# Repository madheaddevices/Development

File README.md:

# Development
 - Under development files
 - Default configuration files
 - In-progress designs

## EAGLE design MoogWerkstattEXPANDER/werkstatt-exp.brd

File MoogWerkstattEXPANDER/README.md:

These files are usable for making an Expander for Moog Werkstatt synthesizer.
First of all, the schematic made in Eagle, included the PCB placing, without tracing.
Second, the manufacturing files are loadable to JLCPCB online PCB ordering service.

BOM:
1. Thonkiconn Jack sockets: https://www.thonk.co.uk/shop/3-5mm-jacks/
2. 1x20 pinheader

Tamás Fejes, 14.12.2021.

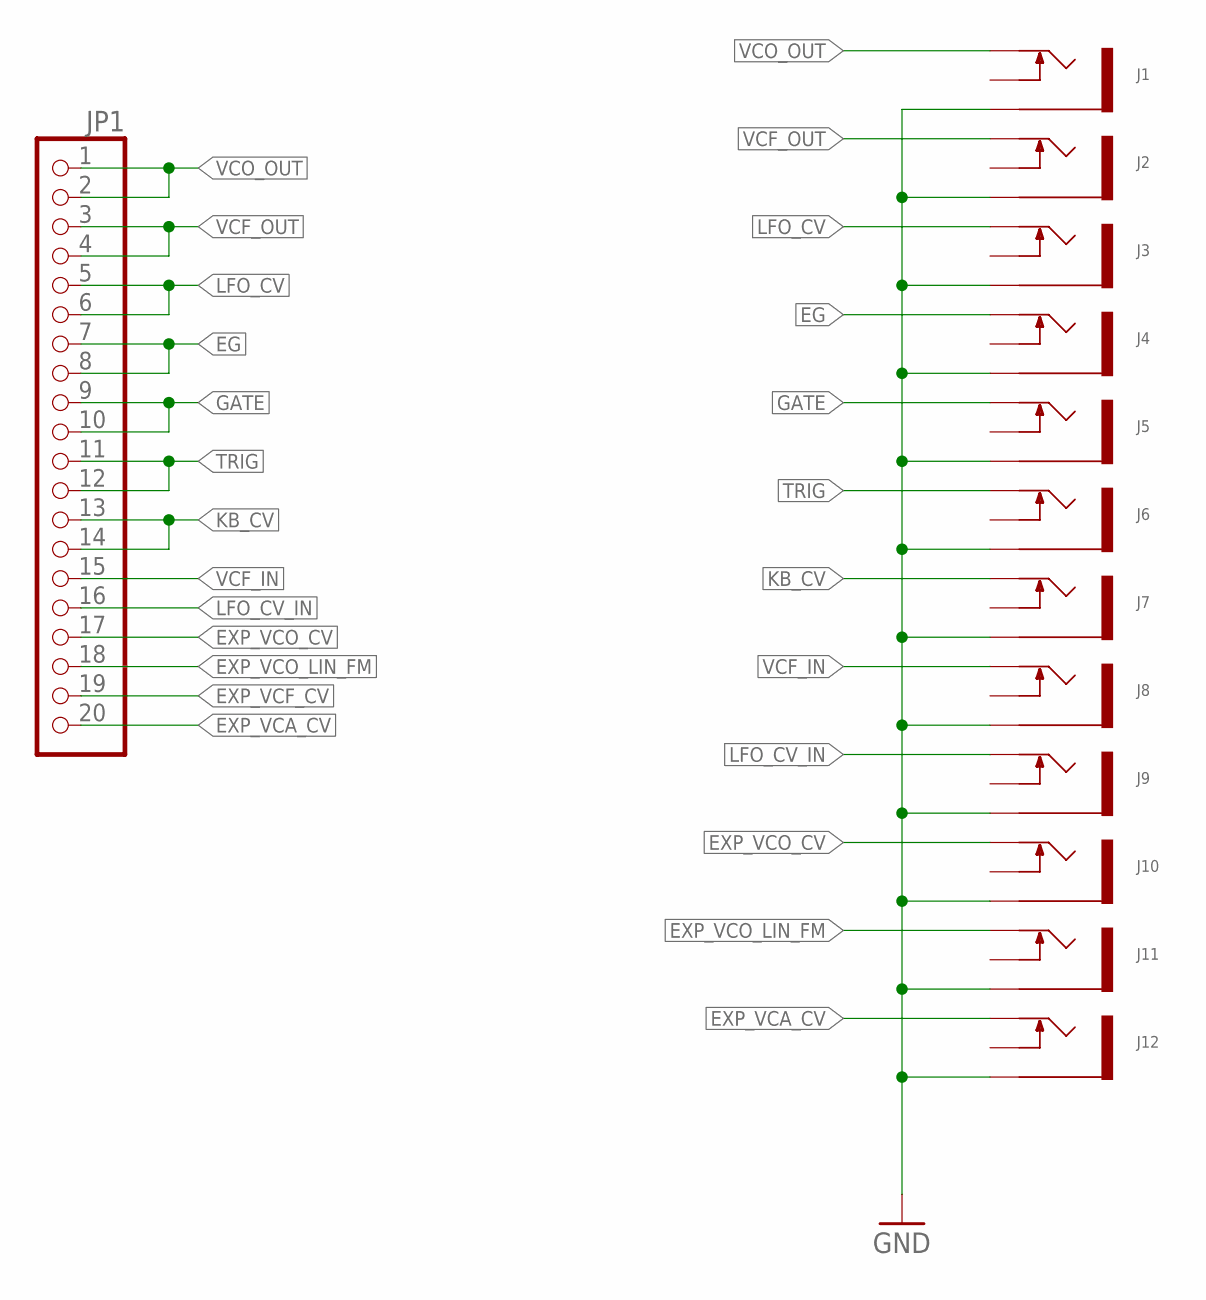
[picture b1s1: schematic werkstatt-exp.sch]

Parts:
J1, J2, J3, J4, J5, J6, J7, J8, J9, J10, J11, J12: THONKICON; WQP-PJ301M-12_JACK
JP1: PINHD-1X20; 1X20

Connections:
EG: J4.3 (2), JP1.7, JP1.8
EXP_VCA_CV: J12.3 (2), JP1.20
EXP_VCF_CV: JP1.19
EXP_VCO_CV: J10.3 (2), JP1.17
EXP_VCO_LIN_FM: J11.3 (2), JP1.18
GATE: J5.3 (2), JP1.9, JP1.10
GND: J1.1, J2.1, J3.1, J4.1, J5.1, J6.1, J7.1, J8.1, J9.1, J10.1, J11.1, J12.1
KB_CV: J7.3 (2), JP1.13, JP1.14
LFO_CV: J3.3 (2), JP1.5, JP1.6
LFO_CV_IN: J9.3 (2), JP1.16
TRIG: J6.3 (2), JP1.11, JP1.12
VCF_IN: J8.3 (2), JP1.15
VCF_OUT: J2.3 (2), JP1.3, JP1.4
VCO_OUT: J1.3 (2), JP1.1, JP1.2

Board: 2 copper layers, 13 parts (0 on the bottom side), 13 nets, no tracks yet.

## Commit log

2021-01-22 Create MINI32MX_default_configuration.cfgsch
    mikroe MINI-32 MX default project settings for test sessions
2021-01-23 Erase all existing data
2021-01-23 MINI-32 MX dev board template project
2021-02-15 DJ stlye tempo bend sync clock
2021-02-17 2021.02.17. update
2021-12-14 Create fff
